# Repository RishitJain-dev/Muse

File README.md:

# Muse
A modern iPod-like device with a micro-SD card slot and a headphone jack, all controlled with a rotary encoder dial, buttons and a screen.

181038.png…]()

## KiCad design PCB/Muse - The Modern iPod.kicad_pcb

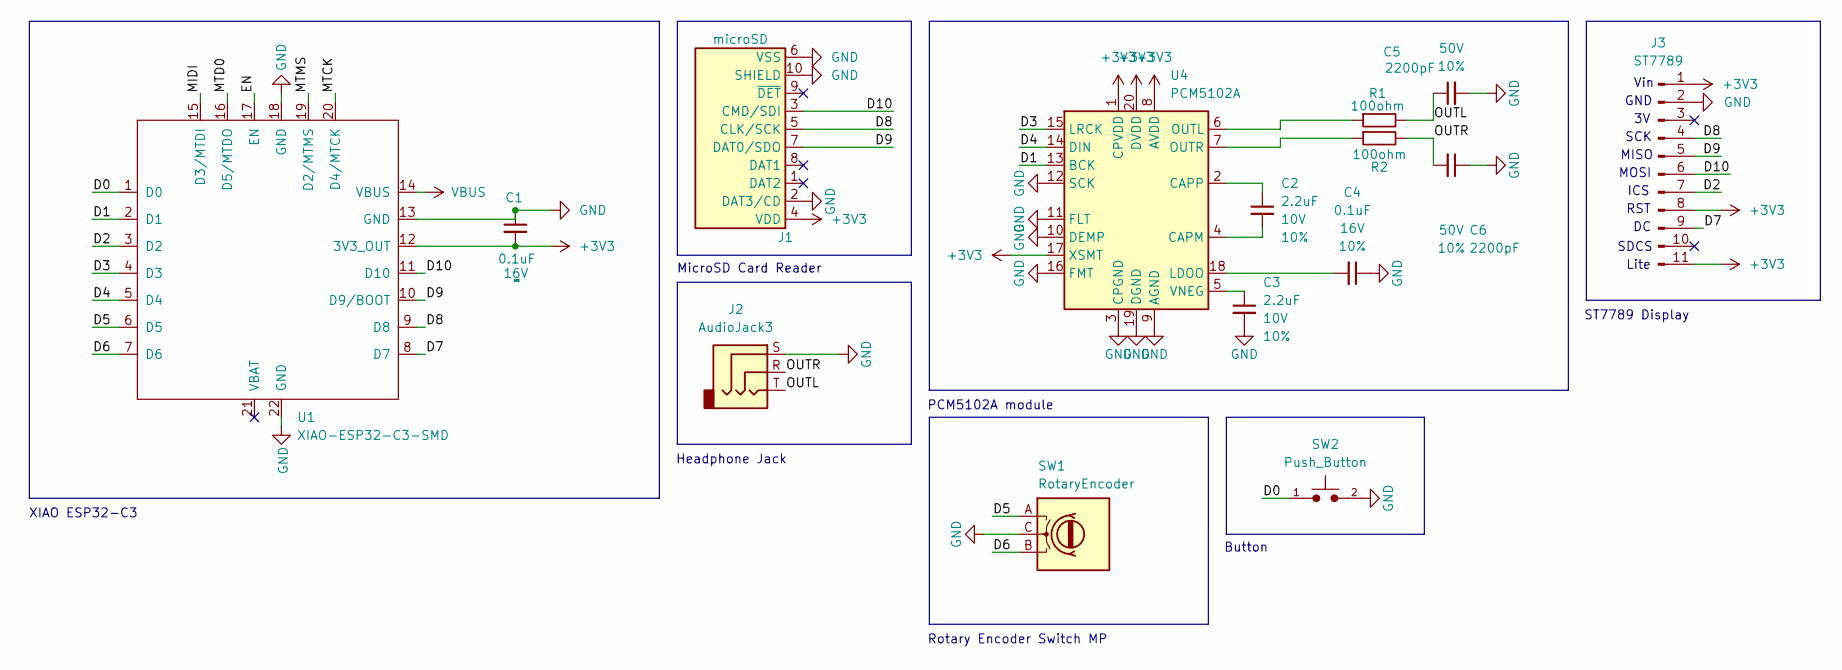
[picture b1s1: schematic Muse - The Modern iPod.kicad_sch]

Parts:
C1, C4: 0.1uF; C_0402_1005Metric; Voltage 16V; Tolerance 10%
C2, C3: 2.2uF; C_0402_1005Metric; Voltage 10V; Tolerance 10%
C5, C6: 2200pF; C_0402_1005Metric; Voltage 50V; Tolerance 10%
J1: microSD; microSD_External_Pin
J2: AudioJack3; Jack_3.5mm_CUI_SJ1-3513N_Horizontal
J3: ST7789; Adafruit 1.9 320x170 Colour IPS TFT Display (ST7789)
R1, R2: 100ohm; R_Axial_DIN0207_L6.3mm_D2.5mm_P10.16mm_Horizontal
SW1: RotaryEncoder; RotaryEncoder_Alps_EC11E_Vertical_H20mm
SW2: Push_Button; SW_PUSH_6mm
U1: XIAO-ESP32-C3-SMD
U4: PCM5102A; TSSOP-20_4.4x6.5mm_P0.65mm

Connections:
+3V3: C1.2, J1.4 (VDD), J3.1, J3.8, J3.11, U1.12 (3V3_OUT), U4.1 (CPVDD), U4.8 (AVDD), U4.17 (XSMT), U4.20 (DVDD)
/D0: SW2.1, U1.1 (D0)
/D1: U1.2 (D1), U4.13 (BCK)
/D2: J3.7, U1.3 (D2)
/D3: U1.4 (D3), U4.15 (LRCK)
/D4: U1.5 (D4), U4.14 (DIN)
/D5: SW1.A, U1.6 (D5)
/D6: SW1.B, U1.7 (D6)
/D7: J3.9, U1.8 (D7)
/D8: J1.5 (CLK/SCK), J3.4, U1.9 (D8)
/D9: J1.7 (DAT0/SDO), J3.5, U1.10 (D9/BOOT)
/D10: J1.3 (CMD/SDI), J3.6, U1.11 (D10)
/EN: U1.17 (EN)
/MIDI: U1.15 (D3/MTDI)
/MTCK: U1.20 (D4/MTCK)
/MTD0: U1.16 (D5/MTDO)
/MTMS: U1.19 (D2/MTMS)
/OUTL: C5.1, J2.T, R1.2
/OUTR: C6.2, J2.R, R2.2
GND: C1.1, C3.2, C4.1, C5.2, C6.1, J1.2 (DAT3/CD), J1.6 (VSS), J1.10 (SHIELD), J2.S, J3.2, SW1.C, SW2.2, U1.13 (GND), U1.18 (GND), U1.22 (GND), U4.3 (CPGND), U4.9 (AGND), U4.10 (DEMP), U4.11 (FLT), U4.12 (SCK), U4.16 (FMT), U4.19 (DGND)
unnamed: C2.2, U4.4 (CAPM)
unnamed: C2.1, U4.2 (CAPP)
unnamed: C4.2, U4.18 (LDOO)
unnamed: R1.1, U4.6 (OUTL)
unnamed: R2.1, U4.7 (OUTR)
unnamed: C3.1, U4.5 (VNEG)
VBUS: U1.14 (VBUS)

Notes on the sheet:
SCK
Rotary Encoder Switch MP
RST
Lite
XIAO ESP32-C3
SDCS
Button
ST7789 Display
MOSI
GND
MISO
PCM5102A module
MicroSD Card Reader
Headphone Jack
ICS
Vin

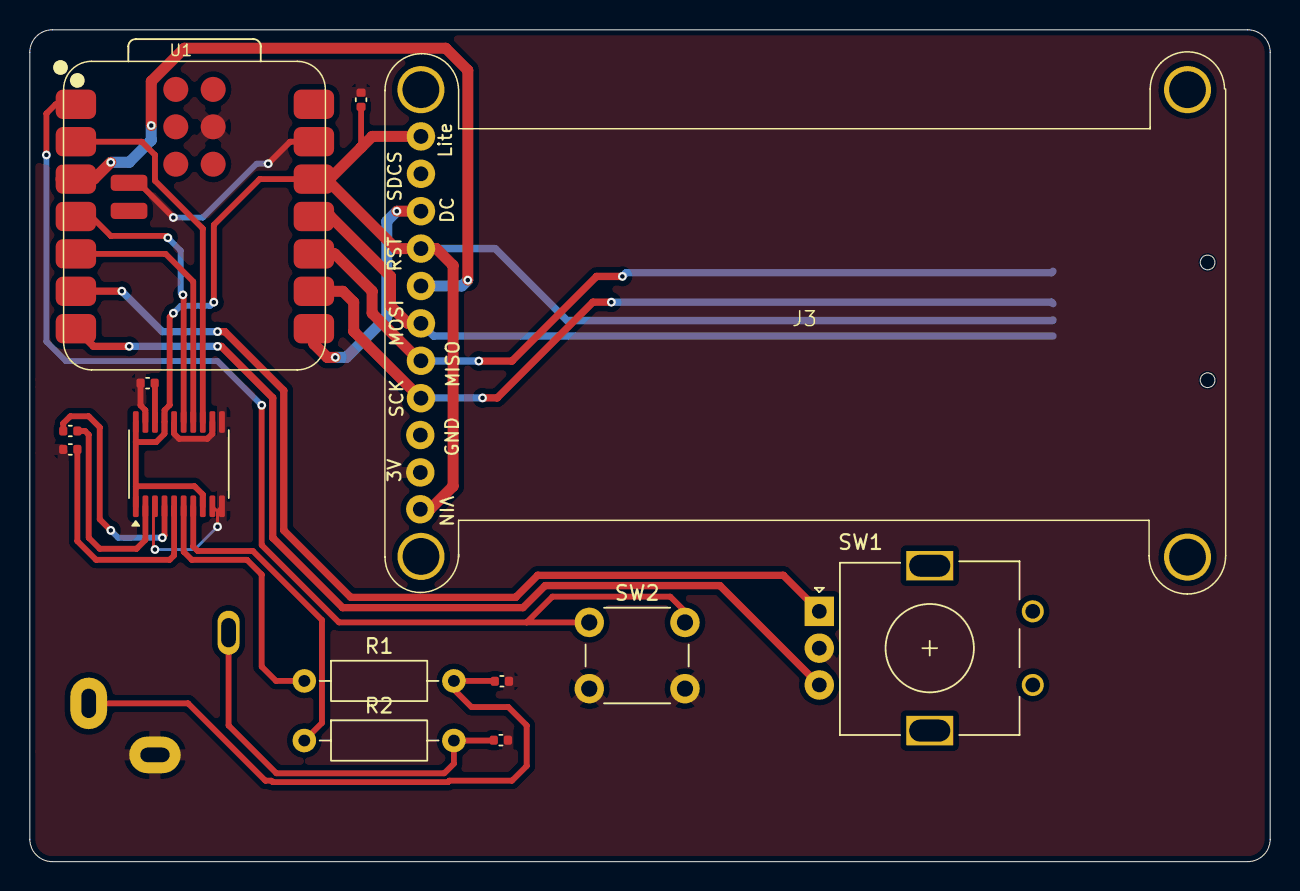
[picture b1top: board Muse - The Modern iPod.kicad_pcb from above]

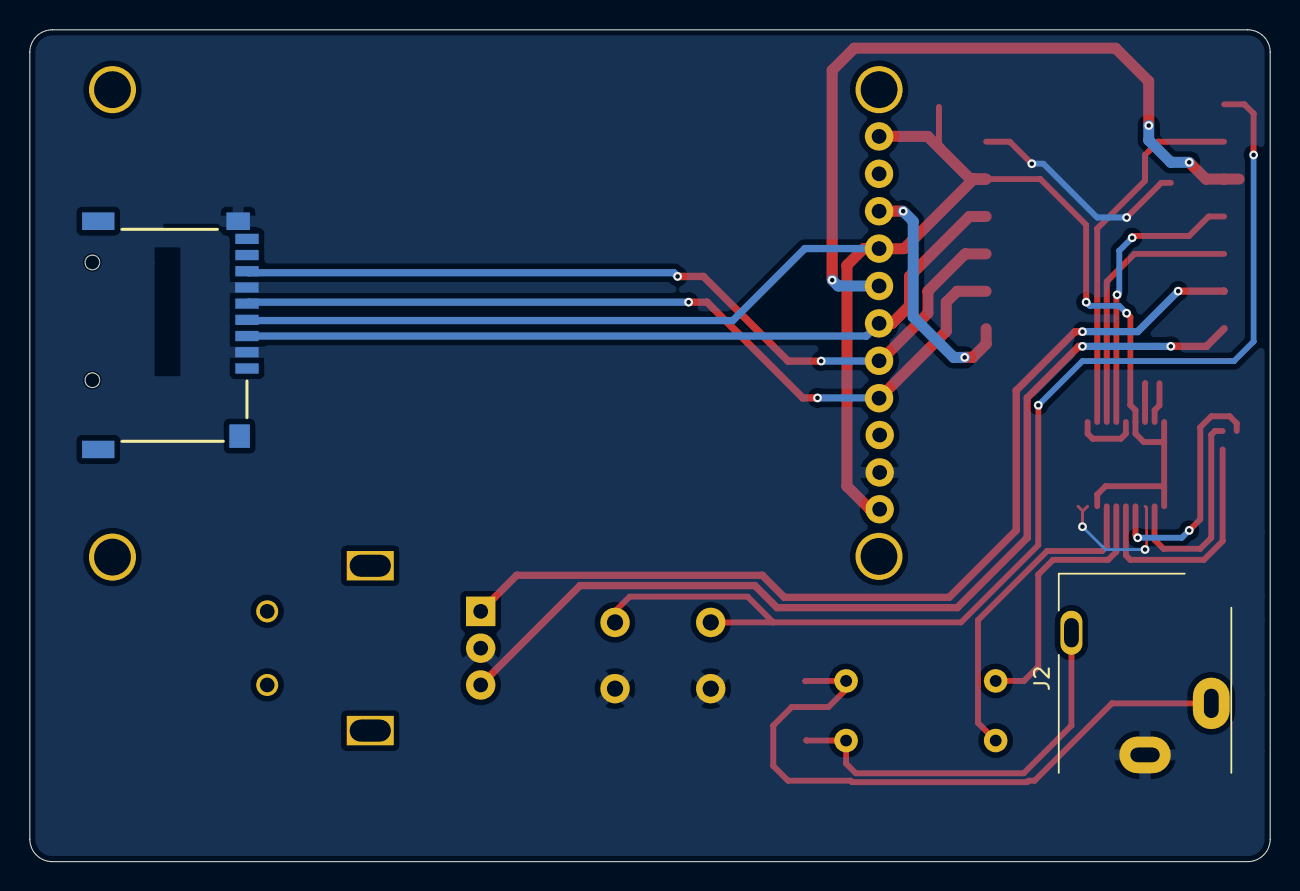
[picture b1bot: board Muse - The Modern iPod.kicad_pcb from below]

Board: 2 copper layers, 84.2 x 56.5 mm, 15 parts (2 on the bottom side), 21 nets.
